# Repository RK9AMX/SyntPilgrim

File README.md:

### HF frequency synthesizer 'Pilgrim'
# Синтезатор ТПП "Пилигрим"
Разработка схемы и ПО: [Oleg 9](http://www.cqham.ru/forum/member.php?3781-Oleg-9)

Разработка печатной платы: [RK9AMX](http://www.cqham.ru/forum/member.php?2533-RK9AMX)

Обсуждение на [форуме](http://www.cqham.ru/forum/showthread.php?45278-%D1%E8%ED%F2%E5%E7%E0%F2%EE%F0-%ED%E0-Si5351%C0-%E4%EB%FF-%D2%CF%CF) cqham.ru

Синтезатор выполнен на базе микросхемы Si5351 и микроконтроллера PIC16F1787 (PIC16F887), индикатор LCD 16x2.

Файл прошивки для **PIC16F887** - 5351_PIC16F887_v07.hex

Для **PIC16F1787** - 5351_PIC16F1787_v07X.hex. С делителем на 8 для валкодера 5351_PIC16F1787_v08X_vlc div 8.hex

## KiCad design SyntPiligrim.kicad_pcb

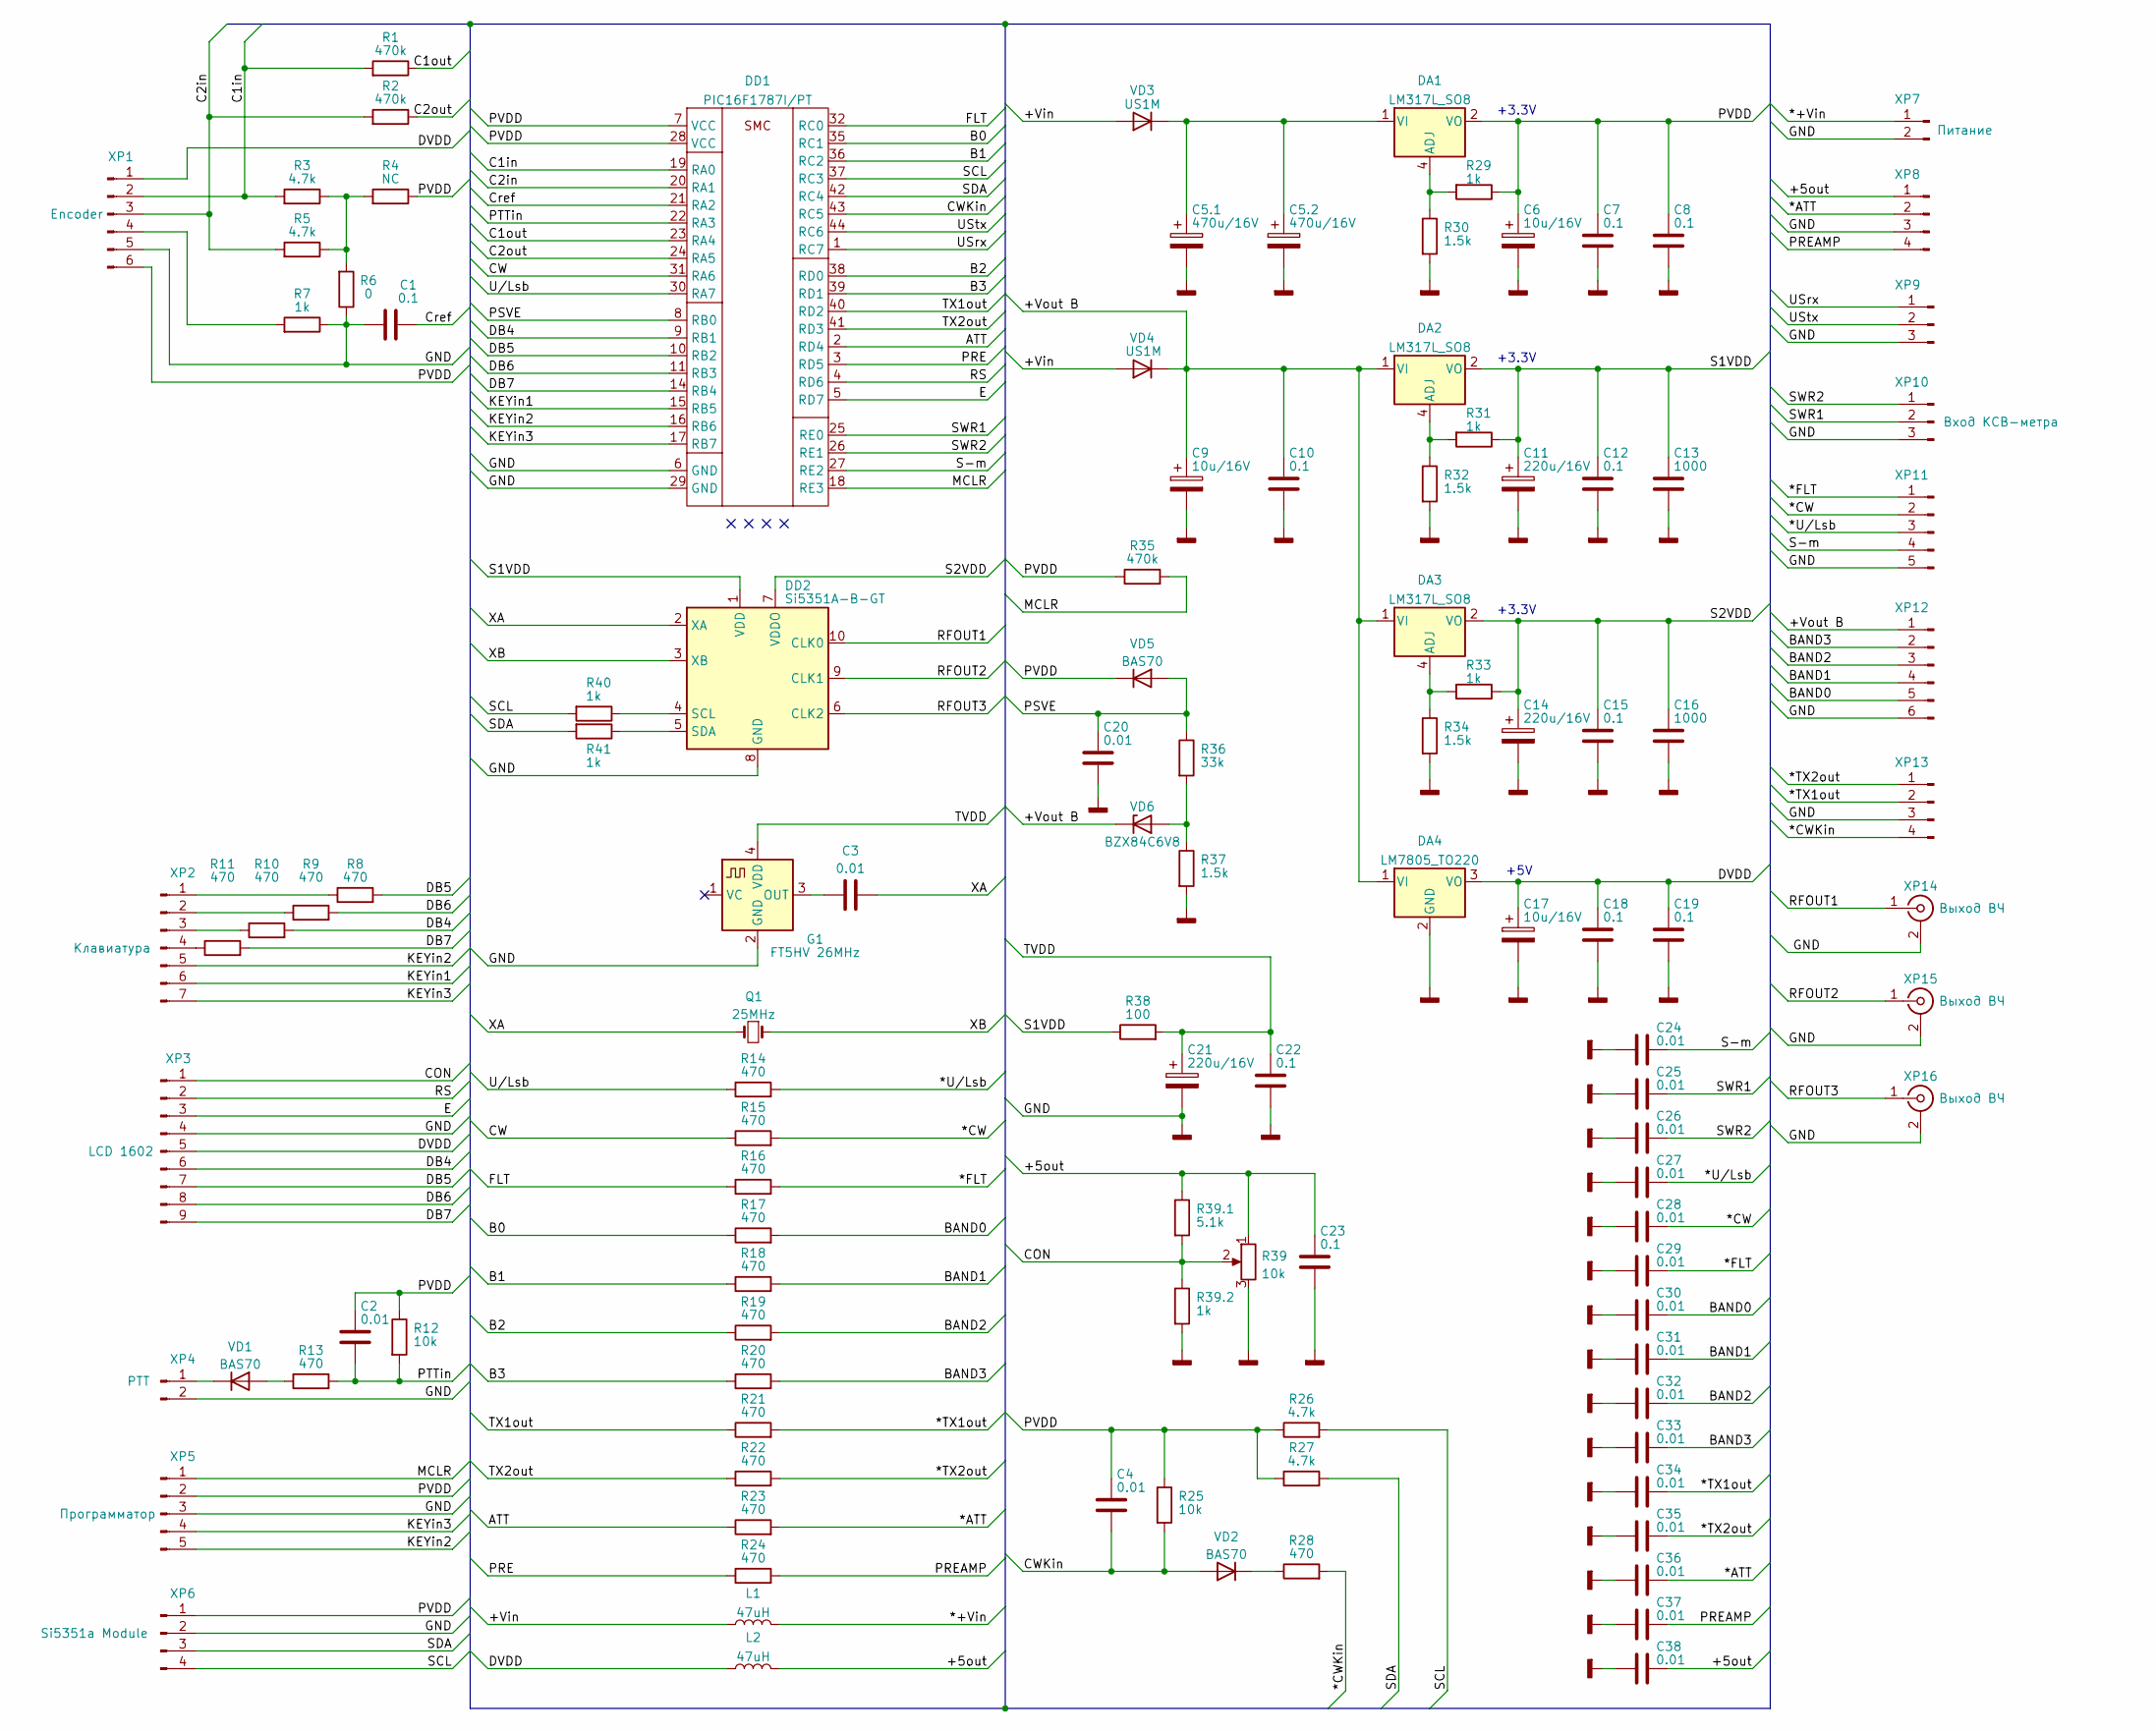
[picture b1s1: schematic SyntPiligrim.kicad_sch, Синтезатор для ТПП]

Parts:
C1, C7, C8, C10, C12, C15, C18, C19, C22, C23: 0.1; C_0805_2012Metric_Pad1.18x1.45mm_HandSolder
C2, C3, C4, C20, C24, C25, C26, C27, C28, C29, C30, C31, C32, C33, C34, C35, C36, C37, C38: 0.01; C_0805_2012Metric_Pad1.18x1.45mm_HandSolder
C5.1, C5.2: 470u/16V; CP_Elec_10x10
C6, C9, C17: 10u/16V; CP_EIA-6032-28_Kemet-C_Pad2.25x2.35mm_HandSolder
C11, C14, C21: 220u/16V; CP_Elec_6.3x7.7
C13, C16: 1000; C_0805_2012Metric_Pad1.18x1.45mm_HandSolder
DA1, DA2, DA3: LM317L_SO8; SOIC-8_3.9x4.9mm_P1.27mm
DA4: LM7805_TO220; TO-220-3_Horizontal_TabDown
DD1: PIC16F1787I/PT; LQFP-44_10x10mm_P0.8mm
DD2: Si5351A-B-GT; MSOP-10_3x3mm_P0.5mm
G1: FT5HV 26MHz; Oscillator_SMD_Fox_FT5H_5.0x3.2mm
L1, L2: 47uH; L_Radial_D8.7mm_P5.00mm_Fastron_07HCP
Q1: 25MHz; Crystal_HC49-4H_Vertical
R1, R2, R35: 470k; R_0805_2012Metric_Pad1.20x1.40mm_HandSolder
R3, R5, R26, R27: 4.7k; R_0805_2012Metric_Pad1.20x1.40mm_HandSolder
R4: NC; R_0805_2012Metric_Pad1.20x1.40mm_HandSolder
R6: 0; R_0805_2012Metric_Pad1.20x1.40mm_HandSolder
R7, R29, R31, R33, R39.2, R40, R41: 1k; R_0805_2012Metric_Pad1.20x1.40mm_HandSolder
R8, R9, R10, R11, R13, R14, R15, R16, R17, R18, R19, R20, R21, R22, R23, R24, R28: 470; R_0805_2012Metric_Pad1.20x1.40mm_HandSolder
R12, R25: 10k; R_0805_2012Metric_Pad1.20x1.40mm_HandSolder
R30, R32, R34, R37: 1.5k; R_0805_2012Metric_Pad1.20x1.40mm_HandSolder
R36: 33k; R_0805_2012Metric_Pad1.20x1.40mm_HandSolder
R38: 100; R_1206_3216Metric_Pad1.30x1.75mm_HandSolder
R39: 10k; Potentiometer_Bourns_3296W_Vertical
R39.1: 5.1k; R_0805_2012Metric_Pad1.20x1.40mm_HandSolder
VD1, VD2, VD5: BAS70; D_SOD-323
VD3, VD4: US1M; D_SMA
VD6: BZX84C6V8; SOT-23
XP1: Encoder; PinHeader_1x06_P2.54mm_Vertical
XP2: Клавиатура; PinHeader_1x07_P2.54mm_Vertical
XP3: LCD 1602; PinHeader_1x09_P2.54mm_Vertical
XP4: PTT; PinHeader_1x02_P2.54mm_Vertical
XP5: Программатор; PinHeader_1x05_P2.54mm_Vertical
XP6: Si5351a Module; PinHeader_1x04_P2.54mm_Vertical
XP7: Питание; PinHeader_1x02_P2.54mm_Vertical
XP8, XP13: c; PinHeader_1x04_P2.54mm_Vertical
XP9: Conn_01x03_Male; PinHeader_1x03_P2.54mm_Vertical
XP10: Вход КСВ-метра; PinHeader_1x03_P2.54mm_Vertical
XP11: c; PinHeader_1x05_P2.54mm_Vertical
XP12: c; PinHeader_1x06_P2.54mm_Vertical
XP14, XP15, XP16: Выход ВЧ; SMA_Wurth_60312002114503_Vertical

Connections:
/*+Vin: L1.2, XP7.1
/*ATT: C36.1, R23.2, XP8.2
/*CW: C28.1, R15.2, XP11.2
/*CWKin: R28.2, XP13.4
/*FLT: C29.1, R16.2, XP11.1
/*TX1out: C34.1, R21.2, XP13.2
/*TX2out: C35.1, R22.2, XP13.1
/*U/Lsb: C27.1, R14.2, XP11.3
/+5out: C23.1, C38.1, L2.2, R39.1, R39.1.1, XP8.1
/+Vin: L1.1, VD3.2 (A), VD4.2 (A)
/+Vout B: C9.1, C10.1, DA2.1 (VI), DA3.1 (VI), DA4.1 (VI), VD4.1 (K), VD6.3 (K), XP12.1
/ATT: DD1.2 (RD4), R23.1
/B0: DD1.35 (RC1), R17.1
/B1: DD1.36 (RC2), R18.1
/B2: DD1.38 (RD0), R19.1
/B3: DD1.39 (RD1), R20.1
/BAND0: C30.1, R17.2, XP12.5
/BAND1: C31.1, R18.2, XP12.4
/BAND2: C32.1, R19.2, XP12.3
/BAND3: C33.1, R20.2, XP12.2
/C1in: DD1.19 (RA0), R1.2, R3.2, XP1.2
/C1out: DD1.23 (RA4), R1.1
/C2in: DD1.20 (RA1), R2.2, R5.2, XP1.3
/C2out: DD1.24 (RA5), R2.1
/CON: R39.2, R39.1.2, R39.2.1, XP3.1
/CW: DD1.31 (RA6), R15.1
/CWKin: C4.2, DD1.43 (RC5), R25.2, VD2.2 (A)
/Cref: C1.2, DD1.21 (RA2)
/DB4: DD1.9 (RB1), R10.2, XP3.6
/DB5: DD1.10 (RB2), R8.2, XP3.7
/DB6: DD1.11 (RB3), R9.2, XP3.8
/DB7: DD1.14 (RB4), R11.2, XP3.9
/DVDD: C17.1, C18.1, C19.1, DA4.3 (VO), L2.1, XP1.1, XP3.5
/E: DD1.5 (RD7), XP3.3
/FLT: DD1.32 (RC0), R16.1
/KEYin1: DD1.15 (RB5), XP2.6
/KEYin2: DD1.16 (RB6), XP2.5, XP5.5
/KEYin3: DD1.17 (RB7), XP2.7, XP5.4
/MCLR: DD1.18 (RE3), R35.2, XP5.1
/PRE: DD1.3 (RD5), R24.1
/PREAMP: C37.1, R24.2, XP8.4
/PSVE: C20.1, DD1.8 (RB0), R36.1, VD5.2 (A)
/PTTin: C2.2, DD1.22 (RA3), R12.2, R13.2
/PVDD: C2.1, C4.1, C6.1, C7.1, C8.1, DA1.2 (VO), DA1.3 (VO), DA1.6 (VO), DA1.7 (VO), DD1.7 (VCC), DD1.28 (VCC), R4.1, R12.1, R25.1, R26.1, R27.1, R29.1, R35.1, VD5.1 (K), XP1.6, XP5.2, XP6.1
/RFOUT1: DD2.10 (CLK0), XP14.1 (In)
/RFOUT2: DD2.9 (CLK1), XP15.1 (In)
/RFOUT3: DD2.6 (CLK2), XP16.1 (In)
/RS: DD1.4 (RD6), XP3.2
/S1VDD: C11.1, C12.1, C13.1, DA2.2 (VO), DA2.3 (VO), DA2.6 (VO), DA2.7 (VO), DD2.1 (VDD), R31.1, R38.1
/S2VDD: C14.1, C15.1, C16.1, DA3.2 (VO), DA3.3 (VO), DA3.6 (VO), DA3.7 (VO), DD2.7 (VDDO), R33.1
/S-m: C24.1, DD1.27 (RE2), XP11.4
/SCL: DD1.37 (RC3), R26.2, R40.2, XP6.4
/SDA: DD1.42 (RC4), R27.2, R41.2, XP6.3
/SWR1: C25.1, DD1.25 (RE0), XP10.2
/SWR2: C26.1, DD1.26 (RE1), XP10.1
/TVDD: C21.1, C22.1, G1.4 (VDD), R38.2
/TX1out: DD1.40 (RD2), R21.1
/TX2out: DD1.41 (RD3), R22.1
/USrx: DD1.1 (RC7), XP9.1
/UStx: DD1.44 (RC6), XP9.2
/U/Lsb: DD1.30 (RA7), R14.1
/XA: C3.2, DD2.2 (XA), Q1.2
/XB: DD2.3 (XB), Q1.1
GNDD: C1.1, C5.1.2, C5.2.2, C6.2, C7.2, C8.2, C9.2, C10.2, C11.2, C12.2, C13.2, C14.2, C15.2, C16.2, C17.2, C18.2, C19.2, C20.2, C21.2, C22.2, C23.2, C24.2, C25.2, C26.2, C27.2, C28.2, C29.2, C30.2, C31.2, C32.2, C33.2, C34.2, C35.2, C36.2, C37.2, C38.2, DA4.2 (GND), DD1.6 (GND), DD1.29 (GND), DD2.8 (GND), G1.2 (GND), R6.1, R7.1, R30.2, R32.2, R34.2, R37.2, R39.3, R39.2.2, XP1.5, XP3.4, XP4.2, XP5.3, XP6.2, XP7.2, XP8.3, XP9.3, XP10.3, XP11.5, XP12.6, XP13.3, XP14.2 (Ext), XP15.2 (Ext), XP16.2 (Ext)
unnamed: C3.1, G1.3 (OUT)
unnamed: C5.1.1, C5.2.1, DA1.1 (VI), VD3.1 (K)
unnamed: DA1.4 (ADJ), R29.2, R30.1
unnamed: DA2.4 (ADJ), R31.2, R32.1
unnamed: DA3.4 (ADJ), R33.2, R34.1
unnamed: DD2.4 (SCL), R40.1
unnamed: DD2.5 (SDA), R41.1
unnamed: R3.1, R4.2, R5.1, R6.2
unnamed: R7.2, XP1.4
unnamed: R8.1, XP2.1
unnamed: R9.1, XP2.2
unnamed: R10.1, XP2.3
unnamed: R11.1, XP2.4
unnamed: R13.1, VD1.2 (A)
unnamed: R28.1, VD2.1 (K)
unnamed: R36.2, R37.1, VD6.1 (A)
unnamed: VD1.1 (K), XP4.1

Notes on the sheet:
+3.3V
+5V

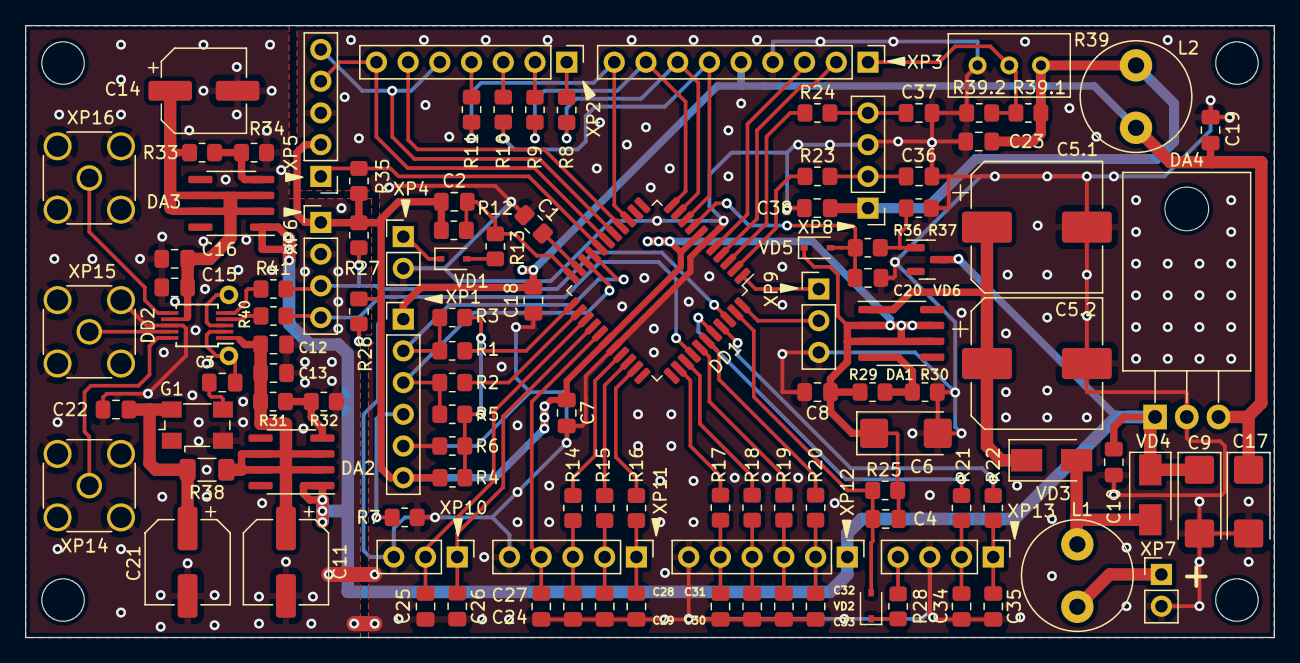
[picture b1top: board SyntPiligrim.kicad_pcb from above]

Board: 2 copper layers, 100.0 x 49.0 mm, 114 parts (1 on the bottom side), 81 nets.

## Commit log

2024-08-13 Добавлена версия 1.10. Добвлено ПО RIG Pilgrim
    Синтезатор для ТПП v.1.10
    Реализован CAT (Kenwood TS-590 limit).
    Реализовано изменение частоты в зависимости от скорости вращения валкодера.
    Изменены фукции кнопок.
    Прочие правки.
